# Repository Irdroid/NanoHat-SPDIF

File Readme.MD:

# NanoHat SPDIF - SPDIF HAT for NanoPI NEO/NEO2 SBCs and custom BuildRoot Distribution

NanoHat SPDIF is a custom BuildRoot Linux Distribution for NanoPi NEO / NEO2 series of embedded development boards.

  - Built in SPDIF output driver
  - SPDIF supported output rates :44k,48k,192k,384k,768k, selected via alsamixer
  - Built in MPD/UPMPDCLI (Stream from any DLNA device to the NanoHAT SPDIF)
  - Built in ShairPortSync (Stream from any Apple device via AirPlay to the NanoHat SPDIF)

# Downloads (Google Drive)

  - https://drive.google.com/drive/folders/117LvP53B9QVHNVw6FJSuzVPkvi4WkGF4?usp=sharing

# Building

  - Clone / Download the repository
  - Download the patched kernel from the google drive link above 
  - Copy the kernel archive in buildroot/dl
  - Make V=s
  - After the build process completes you image will be in buildroot/output/images

# You can Purchase NanoHAT SPDIF module from:

  - https://hwgroup-bg.com/nanohat-spdif

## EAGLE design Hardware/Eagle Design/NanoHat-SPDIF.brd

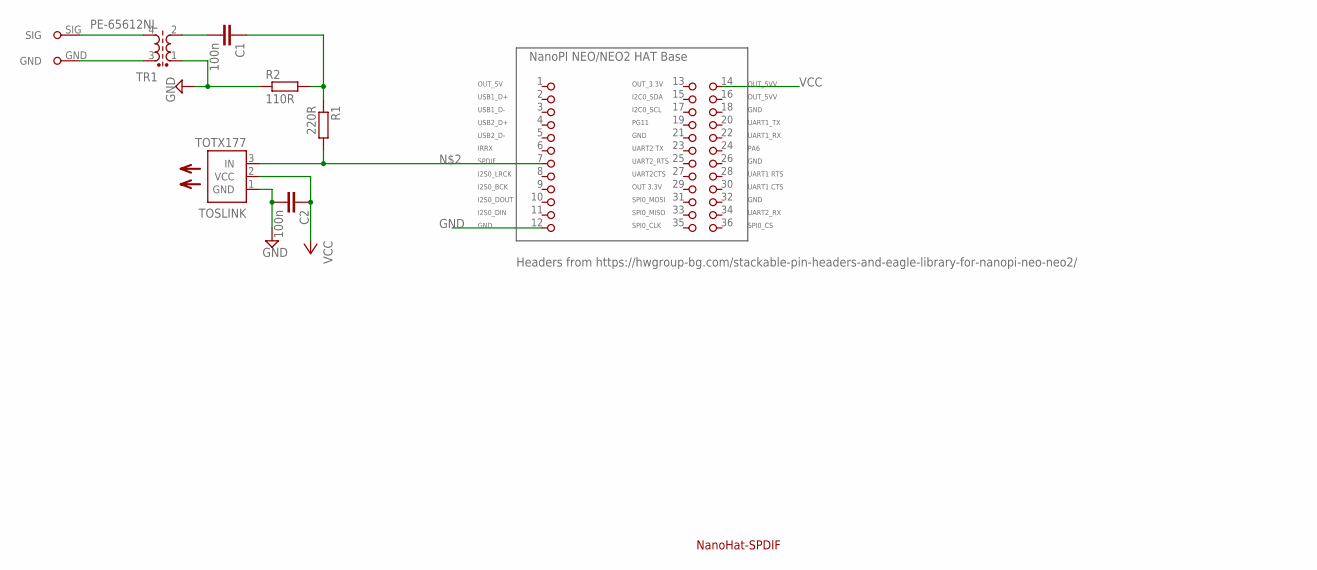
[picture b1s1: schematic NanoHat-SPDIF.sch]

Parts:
C1, C2: 100n; C025-024X044
R1: 220R; R0805
R2: 110R; R0805
TOSLINK: TOTX177; TOTX
TR1: PE-65612NL; S22083
U$1: NANO; NANOPI_NEO_HAT
U$2: AV-8.4-5; AUDIO

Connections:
GND: C2.2, R2.1, TOSLINK.1 (GND), TR1.1, U$1.12 (GND_12)
GROUND: TR1.3, U$2.GND
unnamed: C1.2, TR1.2
unnamed: R1.2, TOSLINK.3 (IN), U$1.7 (SPDIF_P_7)
unnamed: C1.1, R1.1, R2.2
SIG: TR1.4, U$2.SIG
VCC: C2.1, TOSLINK.2 (VCC), U$1.14 (OUT_5V_14)

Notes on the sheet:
Headers from https://hwgroup-bg.com/stackable-pin-headers-and-eagle-library-for-nanopi-neo-neo2/
NanoHat-SPDIF

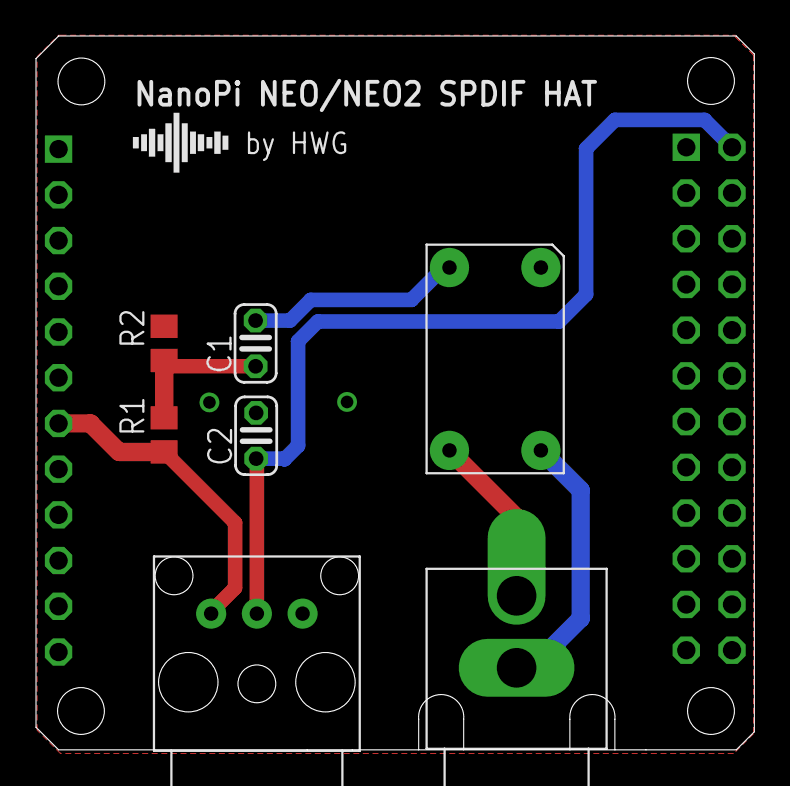
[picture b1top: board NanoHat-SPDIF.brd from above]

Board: 2 copper layers, 39.9 x 39.7 mm, 8 parts (0 on the bottom side), 7 nets.

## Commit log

2020-10-23 Initial Commit
    Initial
2020-11-10 Updated Readme
    Updated Readme
2020-11-10 Update Readme
    Update Readme
2020-11-10 Again Readme update :)
    Again Readme update :)
2020-11-11 Added Eagle Design Files & FootPrint libraries
    Added Eagle Design Files & FootPrint libraries
